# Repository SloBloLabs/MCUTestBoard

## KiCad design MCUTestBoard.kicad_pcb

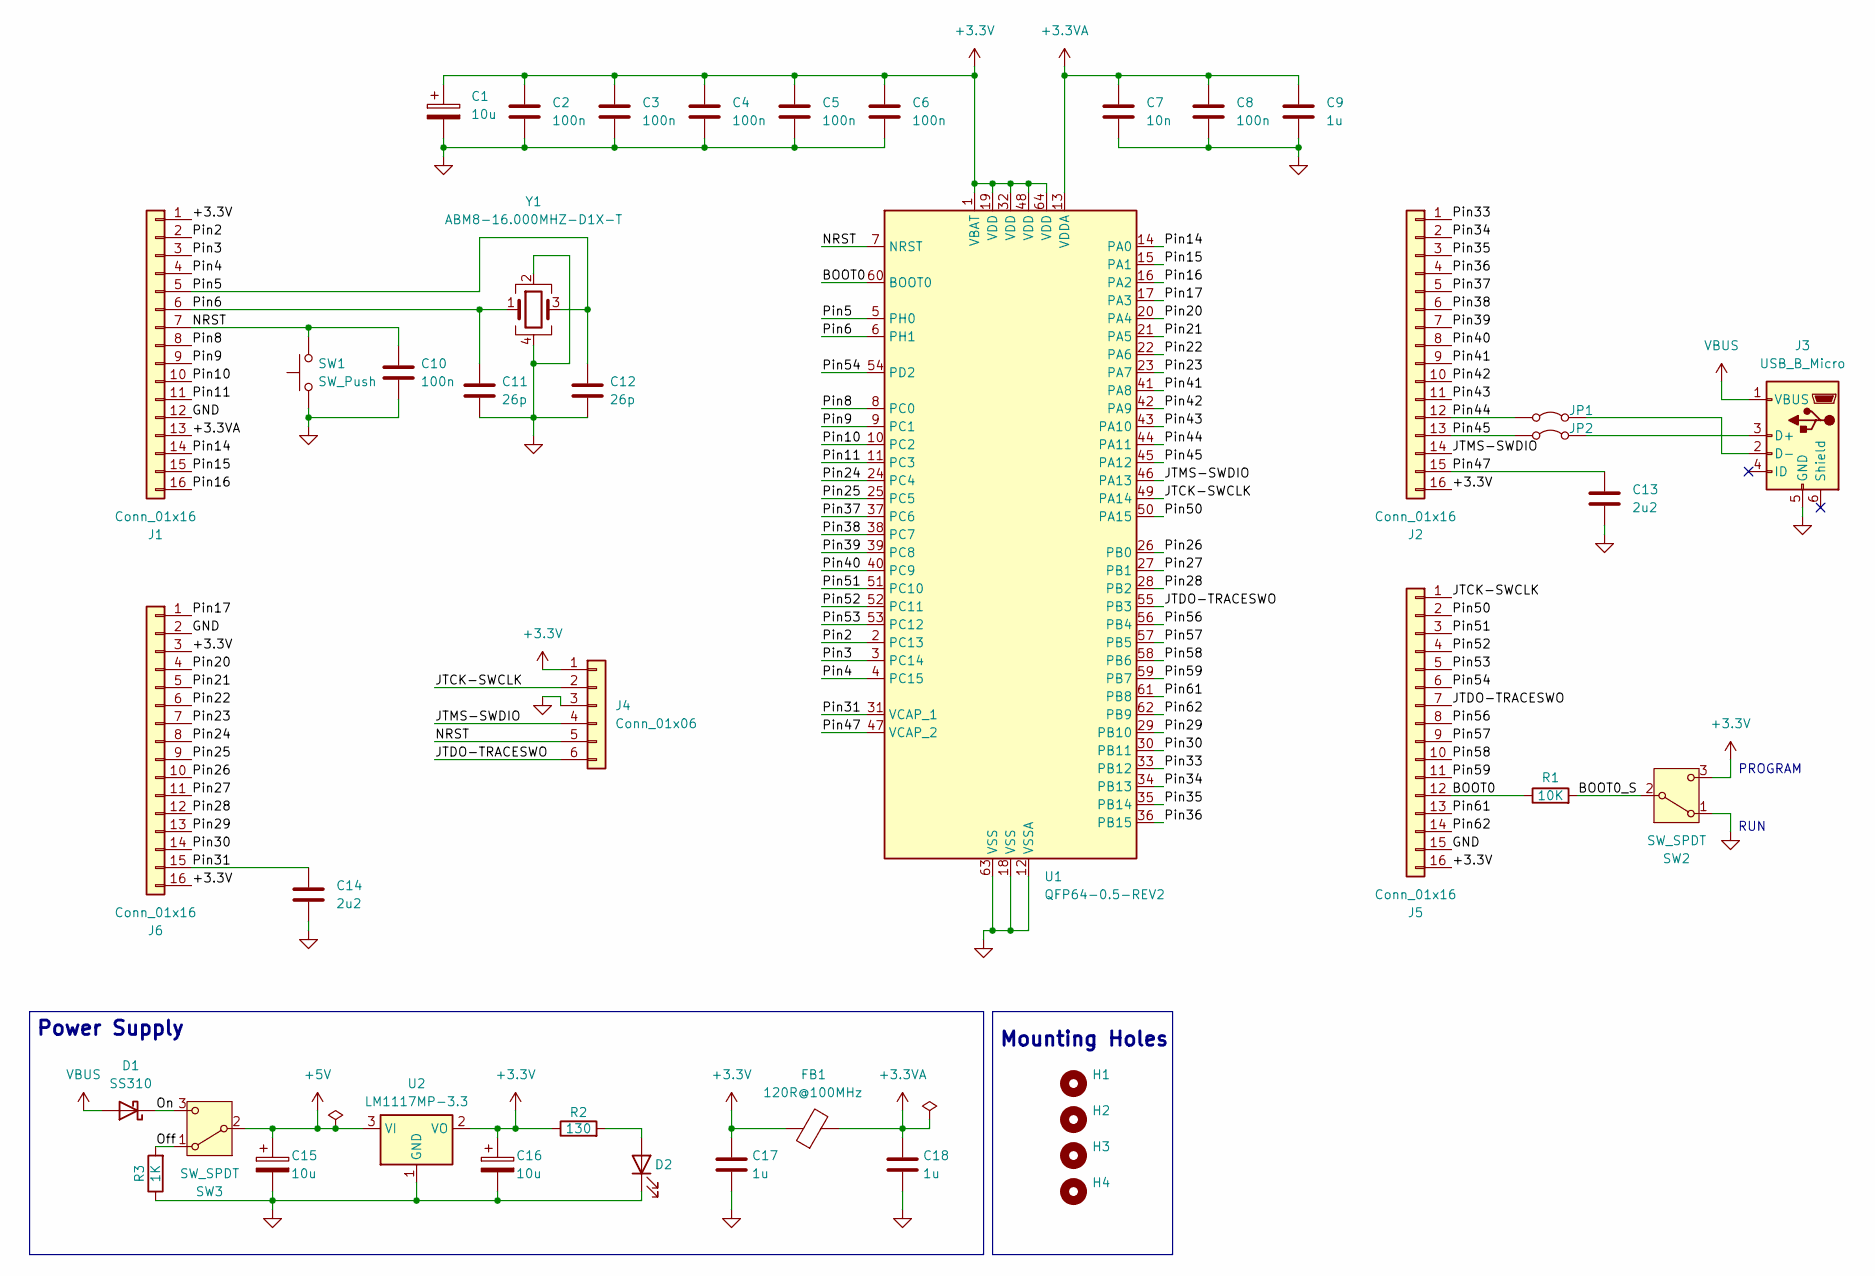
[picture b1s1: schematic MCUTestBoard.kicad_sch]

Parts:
C1, C15, C16: 10u; CP_Radial_D8.0mm_P3.50mm
C2, C3, C4, C5, C6, C8, C10: 100n; C_Rect_L7.2mm_W2.5mm_P5.00mm_FKS2_FKP2_MKS2_MKP2
C7: 10n; C_Rect_L7.2mm_W2.5mm_P5.00mm_FKS2_FKP2_MKS2_MKP2
C9, C17, C18: 1u; C_Rect_L7.2mm_W5.5mm_P5.00mm_FKS2_FKP2_MKS2_MKP2
C11, C12: 26p; C_0603_1608Metric_Pad1.08x0.95mm_HandSolder
C13, C14: 2u2; C_0603_1608Metric_Pad1.08x0.95mm_HandSolder
D1: SS310; D_SMA
D2: LED; LED_D5.0mm_Clear
FB1: 120R@100MHz; L_0603_1608Metric
H1, H2, H3, H4: MountingHole; MountingHole_2.7mm_M2.5
J1, J2, J5, J6: Conn_01x16; PinHeader_1x16_P2.54mm_Vertical
J3: USB_B_Micro; USB_Micro-B_Wuerth_629105150521
J4: Conn_01x06; PinHeader_1x06_P2.54mm_Vertical
JP1, JP2: Jumper_2_Bridged; PinHeader_1x02_P2.54mm_Vertical
R1: 10K; R_Axial_DIN0207_L6.3mm_D2.5mm_P7.62mm_Horizontal
R2: 130; R_Axial_DIN0207_L6.3mm_D2.5mm_P7.62mm_Horizontal
R3: 1K; R_Axial_DIN0207_L6.3mm_D2.5mm_P7.62mm_Horizontal
SW1: SW_Push; E-Switch_TL1105SP
SW2, SW3: SW_SPDT; SW_Toggle_MS500
U1: QFP64-0.5-REV2
U2: LM1117MP-3.3; SOT-223-3_TabPin2
Y1: ABM8-16.000MHZ-D1X-T; Crystal_SMD_3225-4Pin_3.2x2.5mm_HandSoldering

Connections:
+3.3V: C1.1, C2.1, C3.1, C4.1, C5.1, C6.1, C16.1, C17.1, FB1.1, J1.1, J2.16, J4.1, J5.16, J6.3, J6.16, R2.1, SW2.3 (C), U1.1 (VBAT), U1.19 (VDD), U1.32 (VDD), U1.48 (VDD), U1.64 (VDD), U2.2 (VO)
+3.3VA: C7.1, C8.1, C9.1, C18.1, FB1.2, J1.13, U1.13 (VDDA)
+5V: C15.1, SW3.2 (B), U2.3 (VI)
/BOOT0: J5.12, R1.1, U1.60 (BOOT0)
/BOOT0_S: R1.2, SW2.2 (B)
/JTCK-SWCLK: J4.2, J5.1, U1.49 (PA14)
/JTDO-TRACESWO: J4.6, J5.7, U1.55 (PB3)
/JTMS-SWDIO: J2.14, J4.4, U1.46 (PA13)
/NRST: C10.1, J1.7, J4.5, SW1.2, U1.7 (NRST)
/Off: R3.2, SW3.1 (A)
/On: D1.1 (K), SW3.3 (C)
/Pin2: J1.2, U1.2 (PC13)
/Pin3: J1.3, U1.3 (PC14)
/Pin4: J1.4, U1.4 (PC15)
/Pin5: C12.1, J1.5, U1.5 (PH0), Y1.3
/Pin6: C11.1, J1.6, U1.6 (PH1), Y1.1
/Pin8: J1.8, U1.8 (PC0)
/Pin9: J1.9, U1.9 (PC1)
/Pin10: J1.10, U1.10 (PC2)
/Pin11: J1.11, U1.11 (PC3)
/Pin14: J1.14, U1.14 (PA0)
/Pin15: J1.15, U1.15 (PA1)
/Pin16: J1.16, U1.16 (PA2)
/Pin17: J6.1, U1.17 (PA3)
/Pin20: J6.4, U1.20 (PA4)
/Pin21: J6.5, U1.21 (PA5)
/Pin22: J6.6, U1.22 (PA6)
/Pin23: J6.7, U1.23 (PA7)
/Pin24: J6.8, U1.24 (PC4)
/Pin25: J6.9, U1.25 (PC5)
/Pin26: J6.10, U1.26 (PB0)
/Pin27: J6.11, U1.27 (PB1)
/Pin28: J6.12, U1.28 (PB2)
/Pin29: J6.13, U1.29 (PB10)
/Pin30: J6.14, U1.30 (PB11)
/Pin31: C14.1, J6.15, U1.31 (VCAP_1)
/Pin33: J2.1, U1.33 (PB12)
/Pin34: J2.2, U1.34 (PB13)
/Pin35: J2.3, U1.35 (PB14)
/Pin36: J2.4, U1.36 (PB15)
/Pin37: J2.5, U1.37 (PC6)
/Pin38: J2.6, U1.38 (PC7)
/Pin39: J2.7, U1.39 (PC8)
/Pin40: J2.8, U1.40 (PC9)
/Pin41: J2.9, U1.41 (PA8)
/Pin42: J2.10, U1.42 (PA9)
/Pin43: J2.11, U1.43 (PA10)
/Pin44: J2.12, JP1.1 (A), U1.44 (PA11)
/Pin45: J2.13, JP2.1 (A), U1.45 (PA12)
/Pin47: C13.1, J2.15, U1.47 (VCAP_2)
/Pin50: J5.2, U1.50 (PA15)
/Pin51: J5.3, U1.51 (PC10)
/Pin52: J5.4, U1.52 (PC11)
/Pin53: J5.5, U1.53 (PC12)
/Pin54: J5.6, U1.54 (PD2)
/Pin56: J5.8, U1.56 (PB4)
/Pin57: J5.9, U1.57 (PB5)
/Pin58: J5.10, U1.58 (PB6)
/Pin59: J5.11, U1.59 (PB7)
/Pin61: J5.13, U1.61 (PB8)
/Pin62: J5.14, U1.62 (PB9)
GND: C1.2, C2.2, C3.2, C4.2, C5.2, C6.2, C7.2, C8.2, C9.2, C10.2, C11.2, C12.2, C13.2, C14.2, C15.2, C16.2, C17.2, C18.2, D2.1 (K), J1.12, J3.5 (GND), J4.3, J5.15, J6.2, R3.1, SW1.1, SW2.1 (A), U1.12 (VSSA), U1.18 (VSS), U1.63 (VSS), U2.1 (GND), Y1.2, Y1.4
unnamed: D2.2 (A), R2.2
unnamed: J3.3 (D+), JP2.2 (B)
unnamed: J3.2 (D-), JP1.2 (B)
VBUS: D1.2 (A), J3.1 (VBUS)

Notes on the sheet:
RUN
PROGRAM
Mounting Holes
Power Supply

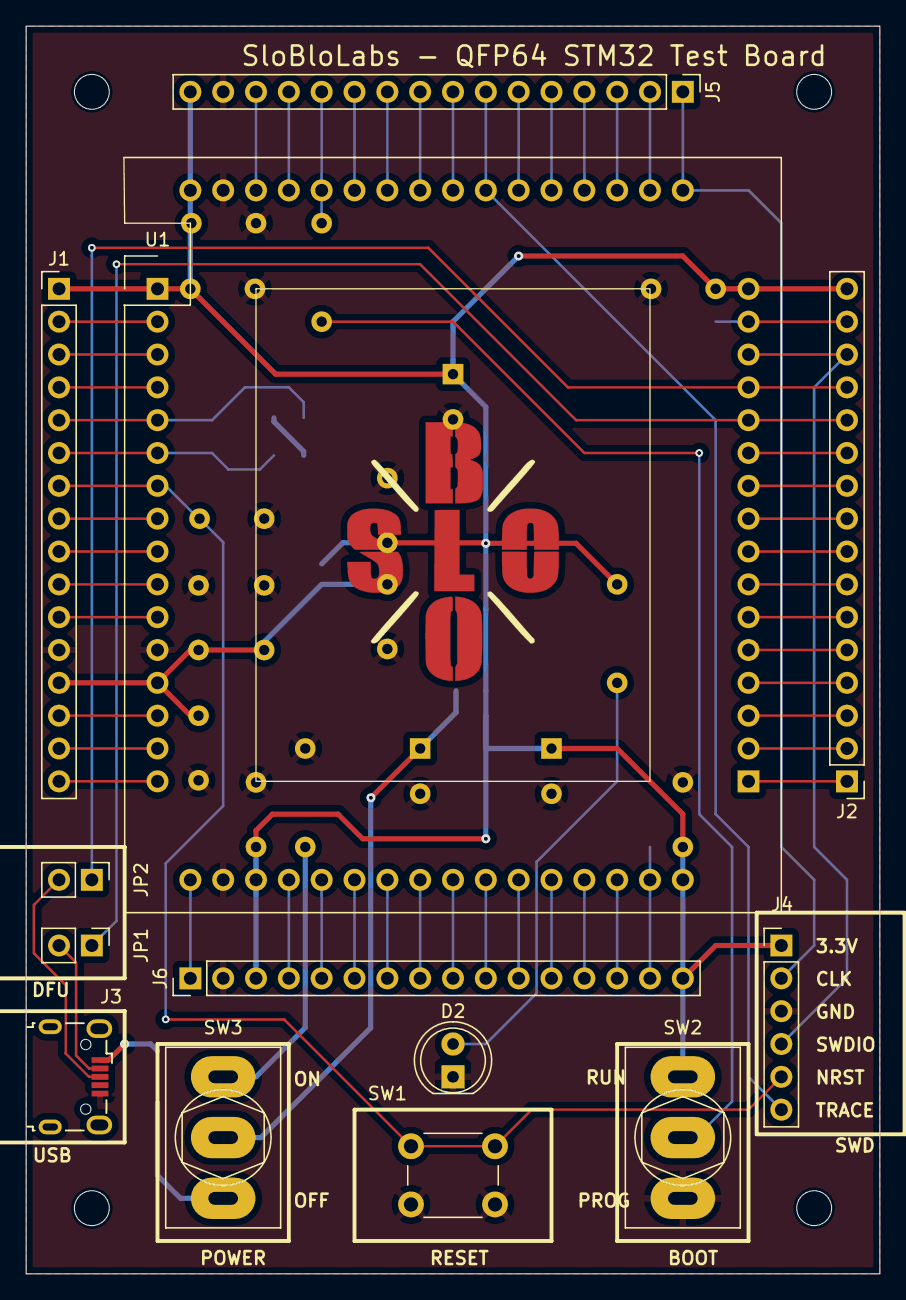
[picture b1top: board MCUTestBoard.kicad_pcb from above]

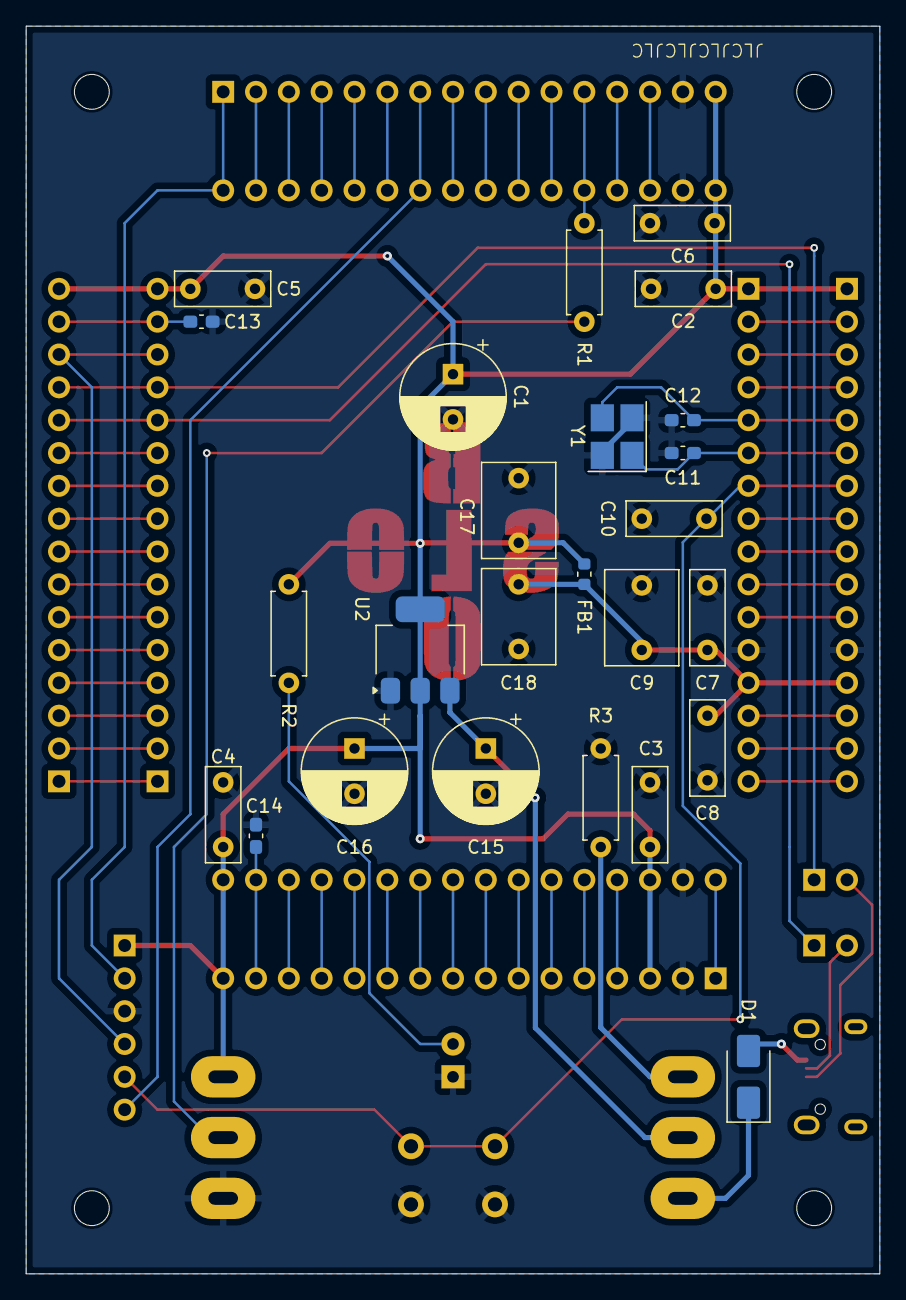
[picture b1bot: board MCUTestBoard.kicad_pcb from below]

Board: 2 copper layers, 66.0 x 96.5 mm, 43 parts (25 on the bottom side), 66 nets.

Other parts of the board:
Ref**: Val**; SloBloLogo_16x20

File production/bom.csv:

Designator,Footprint,Quantity,Value,LCSC Part #
"C1, C15, C16",CP_Radial_D8.0mm_P3.50mm,3,10u,
"C10, C2, C3, C4, C5, C6, C8",C_Rect_L7.2mm_W2.5mm_P5.00mm_FKS2_FKP2_MKS2_MKP2,7,100n,
"C11, C12",0603,2,26p,
"C13, C14",0603,2,2u2,
"C17, C18, C9",C_Rect_L7.2mm_W5.5mm_P5.00mm_FKS2_FKP2_MKS2_MKP2,3,1u,
C7,C_Rect_L7.2mm_W2.5mm_P5.00mm_FKS2_FKP2_MKS2_MKP2,1,10n,
D1,D_SMA,1,SS310,
D2,LED_D5.0mm_Clear,1,LED,
FB1,0603,1,120R@100MHz,
"J1, J2, J5, J6",PinHeader_1x16_P2.54mm_Vertical,4,Conn_01x16,
J3,USB_Micro-B_Wuerth_629105150521,1,USB_B_Micro,
J4,PinHeader_1x06_P2.54mm_Vertical,1,Conn_01x06,
"JP1, JP2",PinHeader_1x02_P2.54mm_Vertical,2,Jumper_2_Bridged,
R1,R_Axial_DIN0207_L6.3mm_D2.5mm_P7.62mm_Horizontal,1,10K,
R2,R_Axial_DIN0207_L6.3mm_D2.5mm_P7.62mm_Horizontal,1,130,
R3,R_Axial_DIN0207_L6.3mm_D2.5mm_P7.62mm_Horizontal,1,1K,
SW1,E-Switch_TL1105SP,1,SW_Push,
"SW2, SW3",SW_Toggle_MS500,2,SW_SPDT,
U1,QFP64-0.5-REV2,1,QFP64-0.5-REV2,
U2,SOT-223-3_TabPin2,1,LM1117MP-3.3,
Y1,Crystal_SMD_3225-4Pin_3.2x2.5mm_HandSoldering,1,ABM8-16.000MHZ-D1X-T,

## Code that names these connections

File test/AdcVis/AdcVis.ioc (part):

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Mcu.Name=STM32F405RGTx
Mcu.Package=LQFP64
Mcu.UserName=STM32F405RGTx
PA0-WKUP.Signal=ADCx_IN0
PA11.Mode=Device_Only
PA11.Signal=USB_OTG_FS_DM
PA12.Mode=Device_Only
PA12.Signal=USB_OTG_FS_DP
PA13.Mode=Serial_Wire
PA13.Signal=SYS_JTMS-SWDIO
PA14.Mode=Serial_Wire
PA14.Signal=SYS_JTCK-SWCLK
PB0.Signal=GPIO_Output
PB1.Signal=GPIO_Output
PB10.Signal=GPIO_Output
PB11.Signal=GPIO_Output
PB12.Signal=GPIO_Output
PB13.Signal=GPIO_Output
PB14.Signal=GPIO_Output
PB15.Signal=GPIO_Output
PB2.Signal=GPIO_Output
PB3.Signal=GPIO_Output
PB4.Signal=GPIO_Output
PB5.Signal=GPIO_Output
PB6.Signal=GPIO_Output
PB7.Signal=GPIO_Output
PB8.Signal=GPIO_Output
PB9.Signal=GPIO_Output
PH0-OSC_IN.Mode=HSE-External-Oscillator
PH0-OSC_IN.Signal=RCC_OSC_IN
PH1-OSC_OUT.Mode=HSE-External-Oscillator
PH1-OSC_OUT.Signal=RCC_OSC_OUT
RCC.HSE_VALUE=16000000
RCC.SYSCLKFreq_VALUE=168000000
RCC.SYSCLKSource=RCC_SYSCLKSOURCE_PLLCLK
board=custom

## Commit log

2025-03-16 Production version 1v00
2025-04-03 LED resistor 150R Add enclosure model add iBom
2025-04-04 Trim width and hight Bevel @ pin connector
2025-04-07 Add a few test projects
2025-04-07 Simple pendulum
2025-04-08 Add AdcVis example (working)
